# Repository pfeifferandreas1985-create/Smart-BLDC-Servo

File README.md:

# Smart BLDC Servo

Ein intelligenter, kompakter Closed-Loop BLDC-Servo-Controller basierend auf:
- **ESP32-C3 Super Mini**
- **SimpleFOC Mini v1.0 (DRV8313)**
- **AS5600 Magnet-Encoder** (I2C)
- **Feetech STS/SCS Emulation** (Half-Duplex 1-Wire UART, 1 Mbps)

Dieses Projekt ist die Weiterentwicklung des `SmartServoStepperV2` und ersetzt den lauten Stepper-Motor durch einen leisen, effizienten Brushless DC (BLDC) Motor (z. B. Gimbal Motoren).

---

## 🛠 Aktueller Entwicklungsstand

Die Hardware-Dokumentation (Schaltplan-Review, detaillierter Verdrahtungsplan, BOM) ist in den Markdown-Dateien `01` bis `06` im Hauptverzeichnis ausführlich dokumentiert.

### Open-Loop Test Tool (NEU!)
Im Verzeichnis `software/OpenLoopTest/` befindet sich das erste Testprogramm. Dieses Tool dient dazu, die grundlegende Hardware (ESP32-C3 + DRV8313 Treiber + BLDC Motor) sicher zu testen, **bevor** Encoder oder Feetech-Bus angeschlossen werden.

**Funktionen des Test-Tools:**
1. **WLAN-Web-Dashboard:** Steuerung des Motors über eine dunkle, professionelle Web-Oberfläche.
2. **Sicherer Open-Loop Modus:** Der Motor läuft im `velocity_openloop` Modus von SimpleFOC. Das Spannungs-Limit ist extrem konservativ gesetzt (2.5V), damit auch Motoren mit niedrigem Widerstand beim "Blockieren" nicht überhitzen.
3. **Hardware-Schutz:** Der Fehler-Pin (`nFLT`) des DRV8313 wird aktiv in Echtzeit vom ESP32-C3 überwacht. Bei Überstrom/Übertemperatur schaltet der ESP32 den Treiber sofort ab.
4. **Alignment:** Beim Start führt der Code automatisch ein elektrisches Alignment (2 rad/s) aus.

**Nutzung:**
1. Öffnen Sie `OpenLoopTest.ino` in der Arduino IDE und flashen Sie es auf den ESP32-C3 (Achtung: `USB CDC On Boot` muss auf `Enabled` stehen!).
2. Verbinden Sie sich mit dem ESP32 über Ihr Netzwerk.
3. Öffnen Sie `software/OpenLoopTest/gui/index.html` lokal im Browser.
4. Geben Sie die IP des ESP32 ein, klicken Sie auf *MOTOR AKTIVIEREN* und regeln Sie die Geschwindigkeit über den Slider.

---

## 🗂 Verzeichnisstruktur

- `software/` - Enthält Firmware (wie z.B. das OpenLoopTest-Tool)
- `software/OpenLoopTest/gui/` - Web-Dashboard für das Test-Tool
- `01_...` bis `06_...` - Ausführliche Baudokumentationen und Pin-Mappings
- `*.kicad_*` - Die KiCad 10.0 Projektdateien für das Hardware-Design

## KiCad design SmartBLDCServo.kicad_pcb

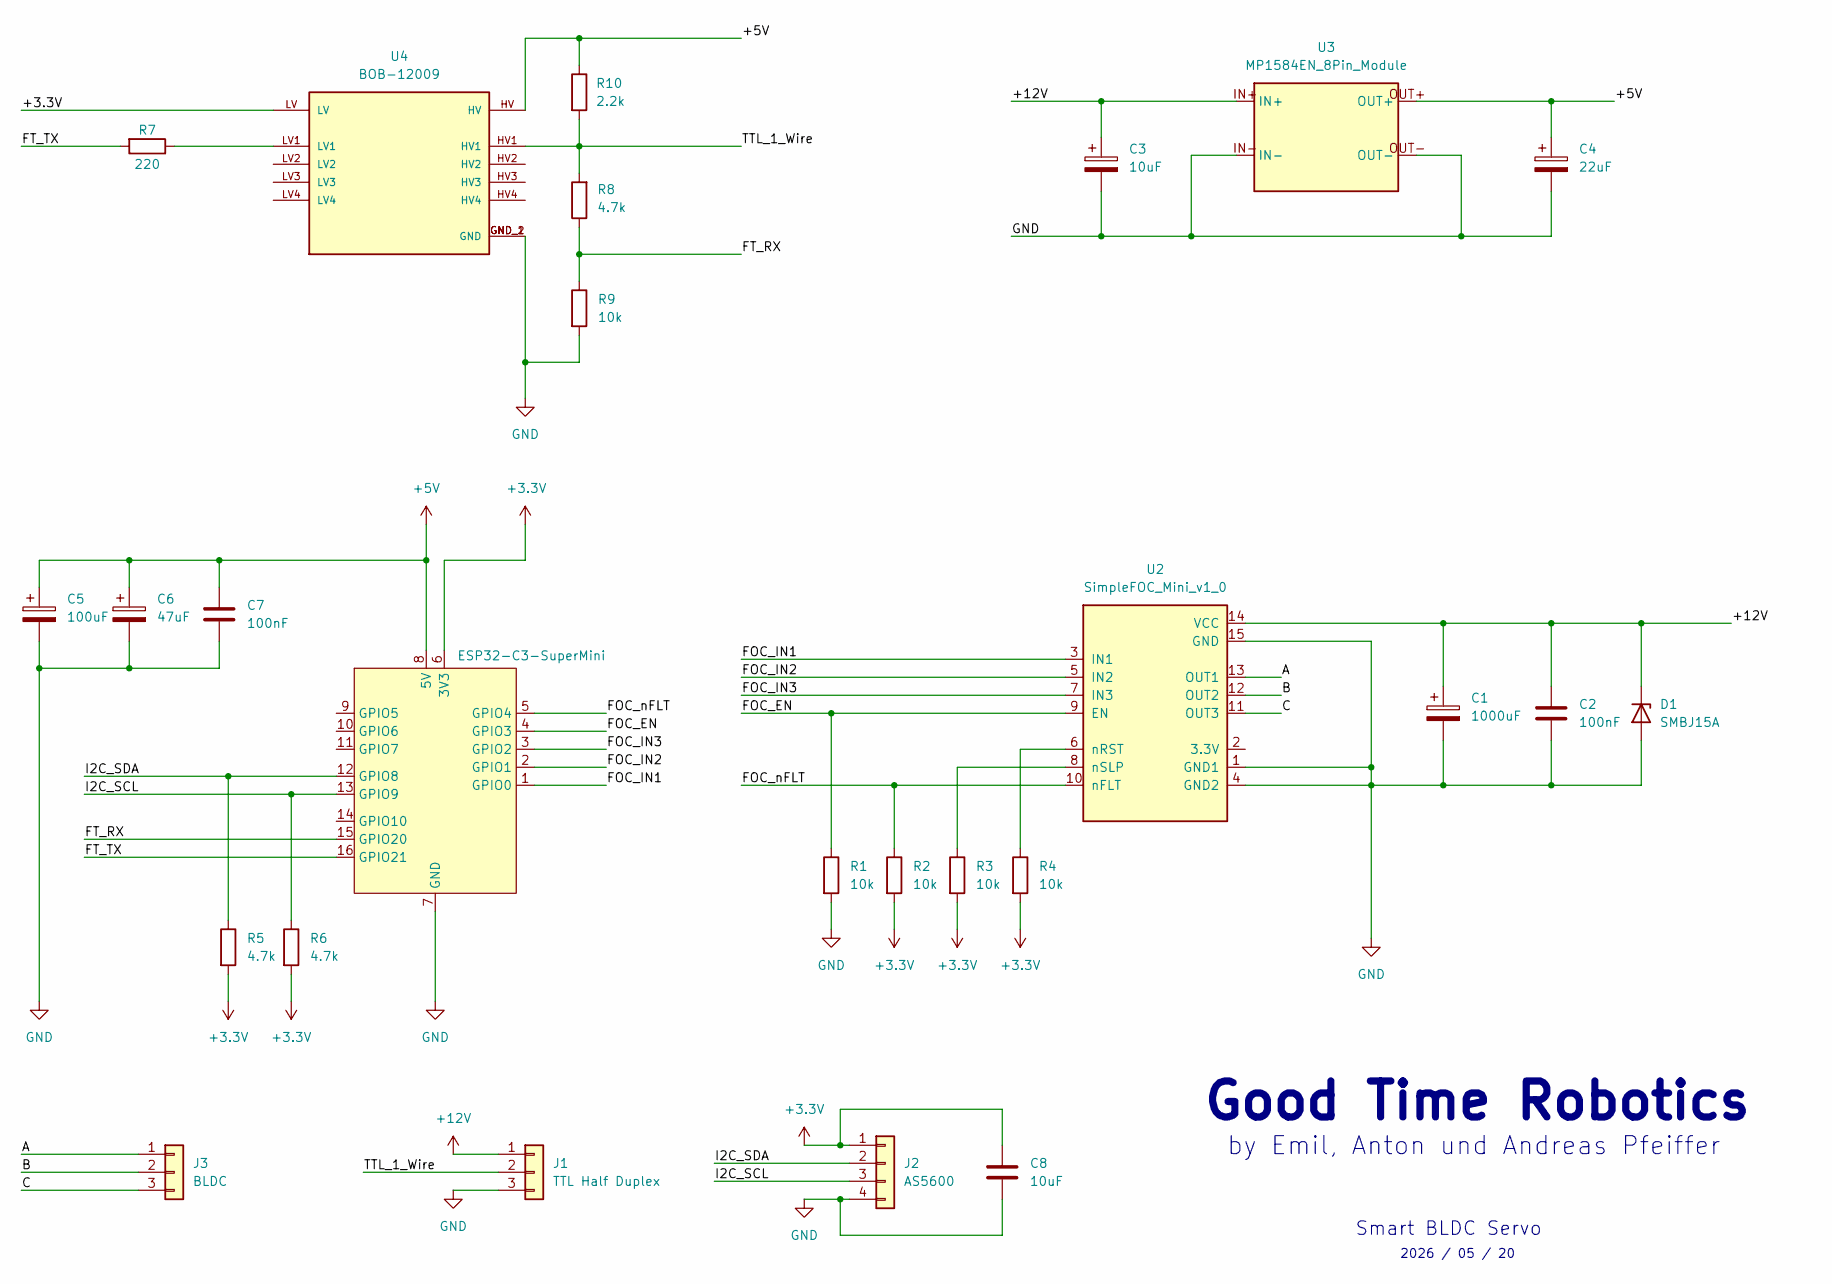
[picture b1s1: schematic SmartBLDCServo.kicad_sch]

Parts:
C1: 1000uF
C2, C7: 100nF; C_Disc_D3.8mm_W2.6mm_P2.50mm
C3: 10uF
C4: 22uF
C5: 100uF
C6: 47uF
C8: 10uF; CP_Radial_D6.3mm_P2.50mm
D1: SMBJ15A; D_SMB
J1: TTL Half Duplex; JST_XH_B3B-XH-A_1x03_P2.50mm_Vertical
J2: AS5600; JST_XH_B4B-XH-A_1x04_P2.50mm_Vertical
J3: BLDC; JST_XH_B3B-XH-A_1x03_P2.50mm_Vertical
R1, R2, R3, R4, R9: 10k; R_Axial_DIN0207_L6.3mm_D2.5mm_P7.62mm_Horizontal
R5, R6, R8: 4.7k; R_Axial_DIN0207_L6.3mm_D2.5mm_P7.62mm_Horizontal
R7: 220; R_Axial_DIN0207_L6.3mm_D2.5mm_P7.62mm_Horizontal
R10: 2.2k; R_Axial_DIN0207_L6.3mm_D2.5mm_P7.62mm_Horizontal
U1: ESP32-C3-SuperMini
U2: SimpleFOC_Mini_v1_0
U3: MP1584EN_8Pin_Module
U4: BOB-12009; CONV_BOB-12009; PARTREV 01

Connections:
+3.3V: C8.2, J2.1, R2.2, R3.2, R4.2, R5.2, R6.2, U1.6 (3V3), U4.LV
+5V: C4.1, C5.1, C6.1, C7.2, R10.1, U1.8 (5V), U3.OUT+, U4.HV
+12V: C1.1, C2.2, C3.1, D1.1 (K), J1.1, U2.14 (VCC), U3.IN+
/A: J3.1, U2.13 (OUT1)
/B: J3.2, U2.12 (OUT2)
/C: J3.3, U2.11 (OUT3)
/FOC_EN: R1.1, U1.4 (GPIO3), U2.9 (EN)
/FOC_IN1: U1.1 (GPIO0), U2.3 (IN1)
/FOC_IN2: U1.2 (GPIO1), U2.5 (IN2)
/FOC_IN3: U1.3 (GPIO2), U2.7 (IN3)
/FOC_nFLT: R2.1, U1.5 (GPIO4), U2.10 (nFLT)
/FT_RX: R8.1, R9.1, U1.15 (GPIO20)
/FT_TX: R7.2, U1.16 (GPIO21)
/I2C_SCL: J2.3, R6.1, U1.13 (GPIO9)
/I2C_SDA: J2.2, R5.1, U1.12 (GPIO8)
/TTL_1_Wire: J1.2, R8.2, R10.2, U4.HV1
GND: C1.2, C2.1, C3.2, C4.2, C5.2, C6.2, C7.1, C8.1, D1.2 (A), J1.3, J2.4, R1.2, R9.2, U1.7 (GND), U2.1 (GND1), U2.4 (GND2), U2.15 (GND), U3.IN-, U3.OUT-, U4.GND_1 (GND), U4.GND_2 (GND)
unnamed: R7.1, U4.LV1
unnamed: R4.1, U2.6 (nRST)
unnamed: R3.1, U2.8 (nSLP)

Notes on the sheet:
Good Time Robotics
2026 / 05 / 20
Smart BLDC Servo
by Emil, Anton und Andreas Pfeiffer

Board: 2 copper layers, 26 parts (0 on the bottom side), 20 nets, no tracks yet.

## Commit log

2026-05-14 Initial commit for Smart BLDC Servo project
2026-05-14 Add Web Serial Dashboard, JSON Telemetry, and BOM Wiring Plan
2026-05-14 Fix 220 Ohm resistor position to LV side
2026-05-20 Update hardware schematic, wiring specs, and firmware with approved protection circuits and split-path level-shifter
2026-05-20 Initialize KiCad 10.0 project cloned from stepper project, renamed to SmartBLDCServo
2026-05-20 Add OpenLoopTest firmware, Web GUI and update project README
2026-05-20 Update KiCad schematic with final TVS diode, capacitor, and FOC_nFLT label additions
2026-05-21 Update KiCad PCB and schematic: Fix footprint UUIDs, add SimpleFOC and MP1584EN footprints
2026-05-21 Add exported Schematic PDF
